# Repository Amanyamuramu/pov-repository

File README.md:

# pov-repository

hd107sを延長可能な基板に搭載したPersistence of Vision（POV）用モジュール

↓レインボーに光らせた様子

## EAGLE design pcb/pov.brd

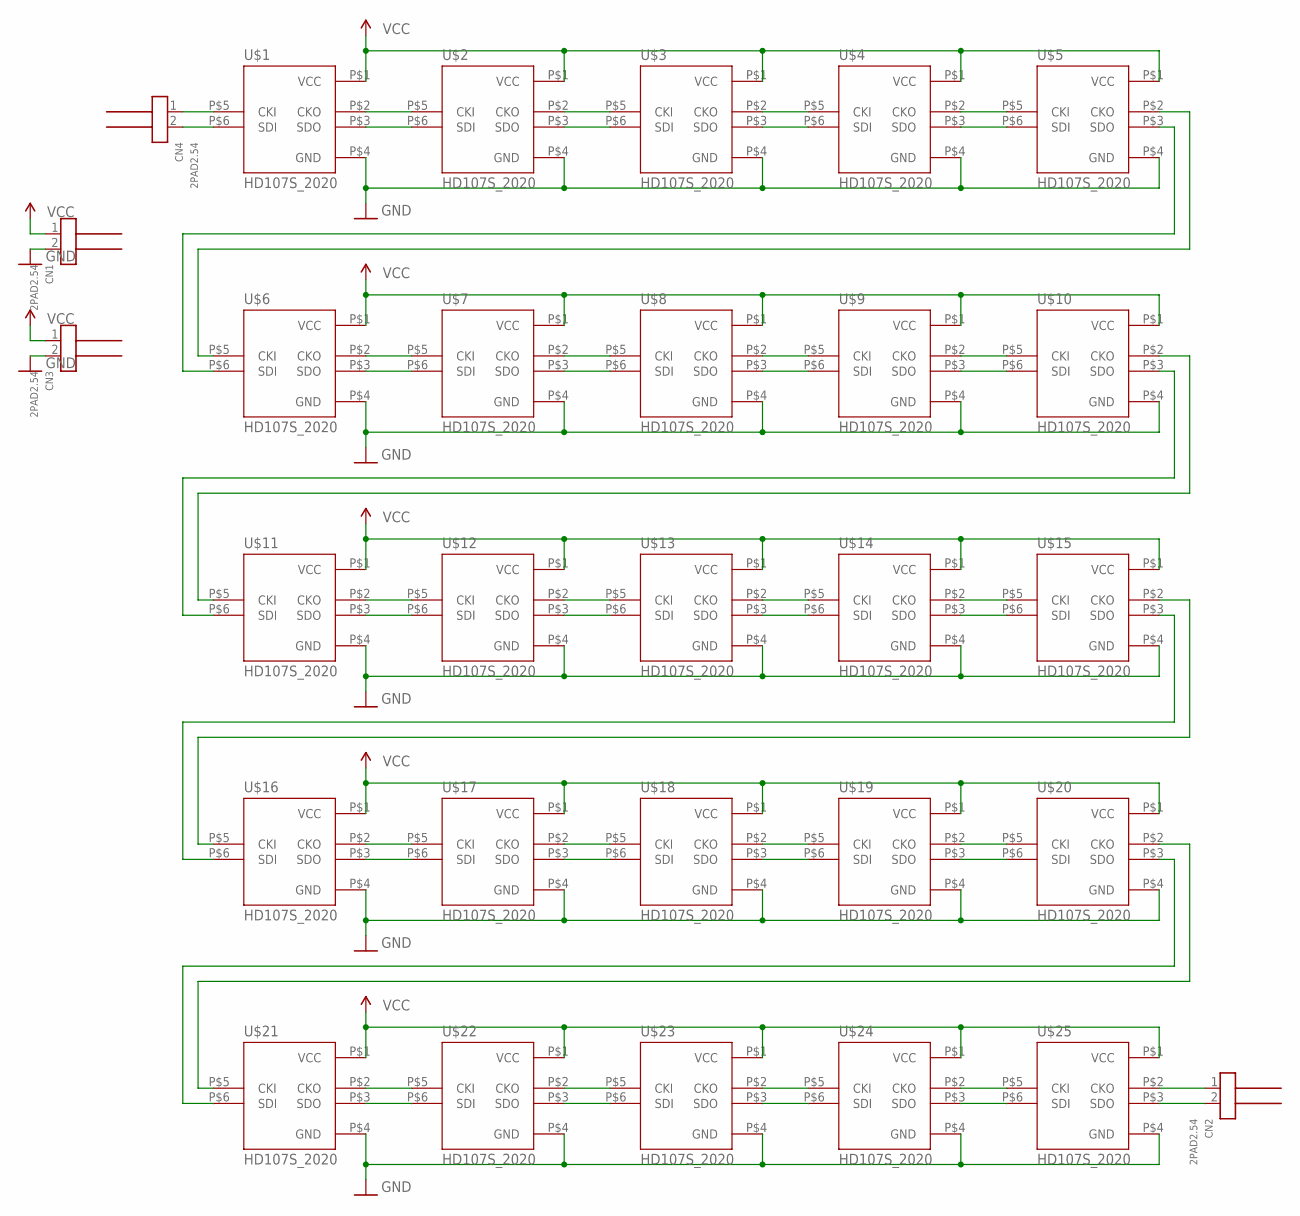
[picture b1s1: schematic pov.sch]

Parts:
CN1, CN2, CN3, CN4: 2PAD2.54; 2POLE_P2.54
U$1, U$2, U$3, U$4, U$5, U$6, U$7, U$8, U$9, U$10, U$11, U$12, U$13, U$14, U$15, U$16, U$17, U$18, U$19, U$20, U$21, U$22, U$23, U$24, U$25: HD107S_2020; HD107S_2020_FOOTPRINT

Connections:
GND: CN1.2, CN3.2, U$1.P$4 (GND), U$2.P$4 (GND), U$3.P$4 (GND), U$4.P$4 (GND), U$5.P$4 (GND), U$6.P$4 (GND), U$7.P$4 (GND), U$8.P$4 (GND), U$9.P$4 (GND), U$10.P$4 (GND), U$11.P$4 (GND), U$12.P$4 (GND), U$13.P$4 (GND), U$14.P$4 (GND), U$15.P$4 (GND), U$16.P$4 (GND), U$17.P$4 (GND), U$18.P$4 (GND), U$19.P$4 (GND), U$20.P$4 (GND), U$21.P$4 (GND), U$22.P$4 (GND), U$23.P$4 (GND), U$24.P$4 (GND), U$25.P$4 (GND)
unnamed: U$1.P$2 (CKO), U$2.P$5 (CKI)
unnamed: U$1.P$3 (SDO), U$2.P$6 (SDI)
unnamed: U$2.P$2 (CKO), U$3.P$5 (CKI)
unnamed: U$2.P$3 (SDO), U$3.P$6 (SDI)
unnamed: U$3.P$2 (CKO), U$4.P$5 (CKI)
unnamed: U$3.P$3 (SDO), U$4.P$6 (SDI)
unnamed: U$4.P$2 (CKO), U$5.P$5 (CKI)
unnamed: U$4.P$3 (SDO), U$5.P$6 (SDI)
unnamed: U$6.P$2 (CKO), U$7.P$5 (CKI)
unnamed: U$6.P$3 (SDO), U$7.P$6 (SDI)
unnamed: U$7.P$2 (CKO), U$8.P$5 (CKI)
unnamed: U$7.P$3 (SDO), U$8.P$6 (SDI)
unnamed: U$8.P$2 (CKO), U$9.P$5 (CKI)
unnamed: U$8.P$3 (SDO), U$9.P$6 (SDI)
unnamed: U$9.P$2 (CKO), U$10.P$5 (CKI)
unnamed: U$9.P$3 (SDO), U$10.P$6 (SDI)
unnamed: U$10.P$3 (SDO), U$11.P$6 (SDI)
unnamed: U$10.P$2 (CKO), U$11.P$5 (CKI)
unnamed: U$11.P$2 (CKO), U$12.P$5 (CKI)
unnamed: U$11.P$3 (SDO), U$12.P$6 (SDI)
unnamed: U$5.P$3 (SDO), U$6.P$6 (SDI)
unnamed: CN4.1, U$1.P$5 (CKI)
unnamed: U$12.P$2 (CKO), U$13.P$5 (CKI)
unnamed: U$12.P$3 (SDO), U$13.P$6 (SDI)
unnamed: U$13.P$2 (CKO), U$14.P$5 (CKI)
unnamed: U$13.P$3 (SDO), U$14.P$6 (SDI)
unnamed: U$14.P$2 (CKO), U$15.P$5 (CKI)
unnamed: U$14.P$3 (SDO), U$15.P$6 (SDI)
unnamed: U$15.P$3 (SDO), U$16.P$6 (SDI)
unnamed: U$15.P$2 (CKO), U$16.P$5 (CKI)
unnamed: U$16.P$2 (CKO), U$17.P$5 (CKI)
unnamed: U$16.P$3 (SDO), U$17.P$6 (SDI)
unnamed: U$17.P$2 (CKO), U$18.P$5 (CKI)
unnamed: U$17.P$3 (SDO), U$18.P$6 (SDI)
unnamed: U$18.P$2 (CKO), U$19.P$5 (CKI)
unnamed: U$18.P$3 (SDO), U$19.P$6 (SDI)
unnamed: U$19.P$2 (CKO), U$20.P$5 (CKI)
unnamed: U$19.P$3 (SDO), U$20.P$6 (SDI)
unnamed: U$20.P$3 (SDO), U$21.P$6 (SDI)
unnamed: U$20.P$2 (CKO), U$21.P$5 (CKI)
unnamed: U$21.P$2 (CKO), U$22.P$5 (CKI)
unnamed: U$21.P$3 (SDO), U$22.P$6 (SDI)
unnamed: U$22.P$2 (CKO), U$23.P$5 (CKI)
unnamed: U$22.P$3 (SDO), U$23.P$6 (SDI)
unnamed: U$23.P$2 (CKO), U$24.P$5 (CKI)
unnamed: U$23.P$3 (SDO), U$24.P$6 (SDI)
unnamed: U$24.P$2 (CKO), U$25.P$5 (CKI)
unnamed: U$24.P$3 (SDO), U$25.P$6 (SDI)
unnamed: CN2.2, U$25.P$3 (SDO)
unnamed: CN2.1, U$25.P$2 (CKO)
unnamed: U$5.P$2 (CKO), U$6.P$5 (CKI)
unnamed: CN4.2, U$1.P$6 (SDI)
VCC: CN1.1, CN3.1, U$1.P$1 (VCC), U$2.P$1 (VCC), U$3.P$1 (VCC), U$4.P$1 (VCC), U$5.P$1 (VCC), U$6.P$1 (VCC), U$7.P$1 (VCC), U$8.P$1 (VCC), U$9.P$1 (VCC), U$10.P$1 (VCC), U$11.P$1 (VCC), U$12.P$1 (VCC), U$13.P$1 (VCC), U$14.P$1 (VCC), U$15.P$1 (VCC), U$16.P$1 (VCC), U$17.P$1 (VCC), U$18.P$1 (VCC), U$19.P$1 (VCC), U$20.P$1 (VCC), U$21.P$1 (VCC), U$22.P$1 (VCC), U$23.P$1 (VCC), U$24.P$1 (VCC), U$25.P$1 (VCC)

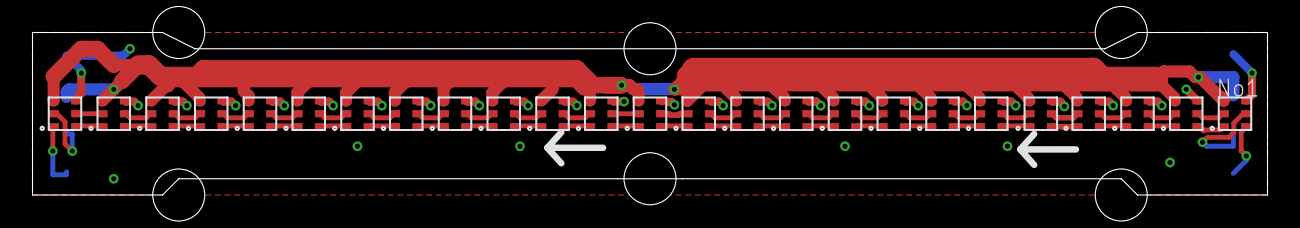
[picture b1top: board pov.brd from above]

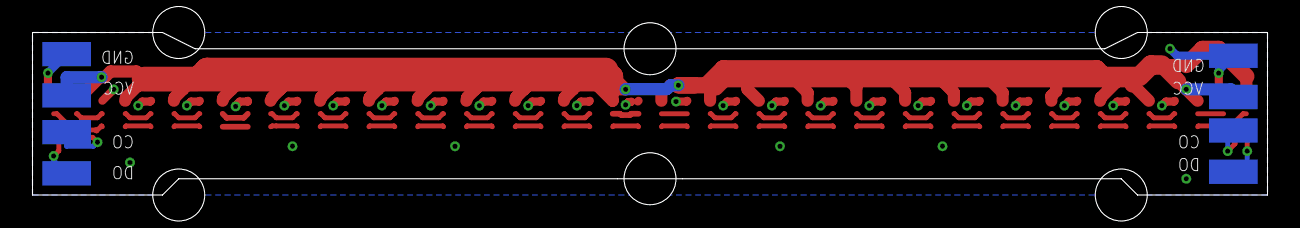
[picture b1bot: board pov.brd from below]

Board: 2 copper layers, 76.0 x 10.0 mm, 29 parts (4 on the bottom side), 54 nets.

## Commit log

2024-10-16 完成品の写真を追加
2024-10-16 arduinoにてpovのカラーを変更するプロジェクトを追加
2024-10-16 xiao_s3にてpovのledを制御プロジェクト追加
2024-10-21 povの羽のモデルを追加

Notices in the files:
parts and their libraries:
SparkFun-PowerSymbols: Licensing: Creative Commons ShareAlike 4.0 International - https://creativecommons.org/licenses/by-sa/4.0
